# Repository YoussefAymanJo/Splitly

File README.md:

## Splitly

## Description

corne  hybrid wireless keyboard based .As it consists of a left part keyboard  connected to pc wired ,and right part keyboard powered by a rechargeable Battery which can operate up to week and connected to left part via bluetooth.And operated by nice Nano and CAT display. And a  numpad with RGB colours, connected wired to pc and powered by pico rp2040 .
## Why it was built
I built this,beacause i always need full split mechanical keyboard,but i need to customize it features by myself.So this keyboard it custosmized to my needings.Also,it has customized features based on usage.Splitly is not just regular keybaord but,desgined to be my companion.
## How to use it / Build it
Firsly,printing all 3d models after that fabricate PCB.After that assemble mx switches,MCU and battery management of pcb.then assemble all this parts together.finally,upload firmware on nice nano and pico,the test all 
## Schematic
I made the schematic and keyboard matrix for the corne keyboard, then the  numpad  .

### Left Part

### Right Part

### Numpad

## PCB
I routed the pcb ,then i outlined the shape of 2 keboard parts and numpad .

### Left Part

### Right Part

### Numpad

## CAD
I started   sketching the plate for left & right part keyboard,the i the Enclosure , then the top cover.After that i worked on numpad  plate, then enclosure and top cover,finally i redered them all.

### Left Part

### Right Part

### Numpad

## Firmware
I used kmk with CircuitPython as firmware,and made code for the left  & right part which is keyboard and the numpad

### Left Part

### Right Part

### Numpad

## BOM 
I made the BOM  and needed materials ,in egypt then convert its price to USD dollar.

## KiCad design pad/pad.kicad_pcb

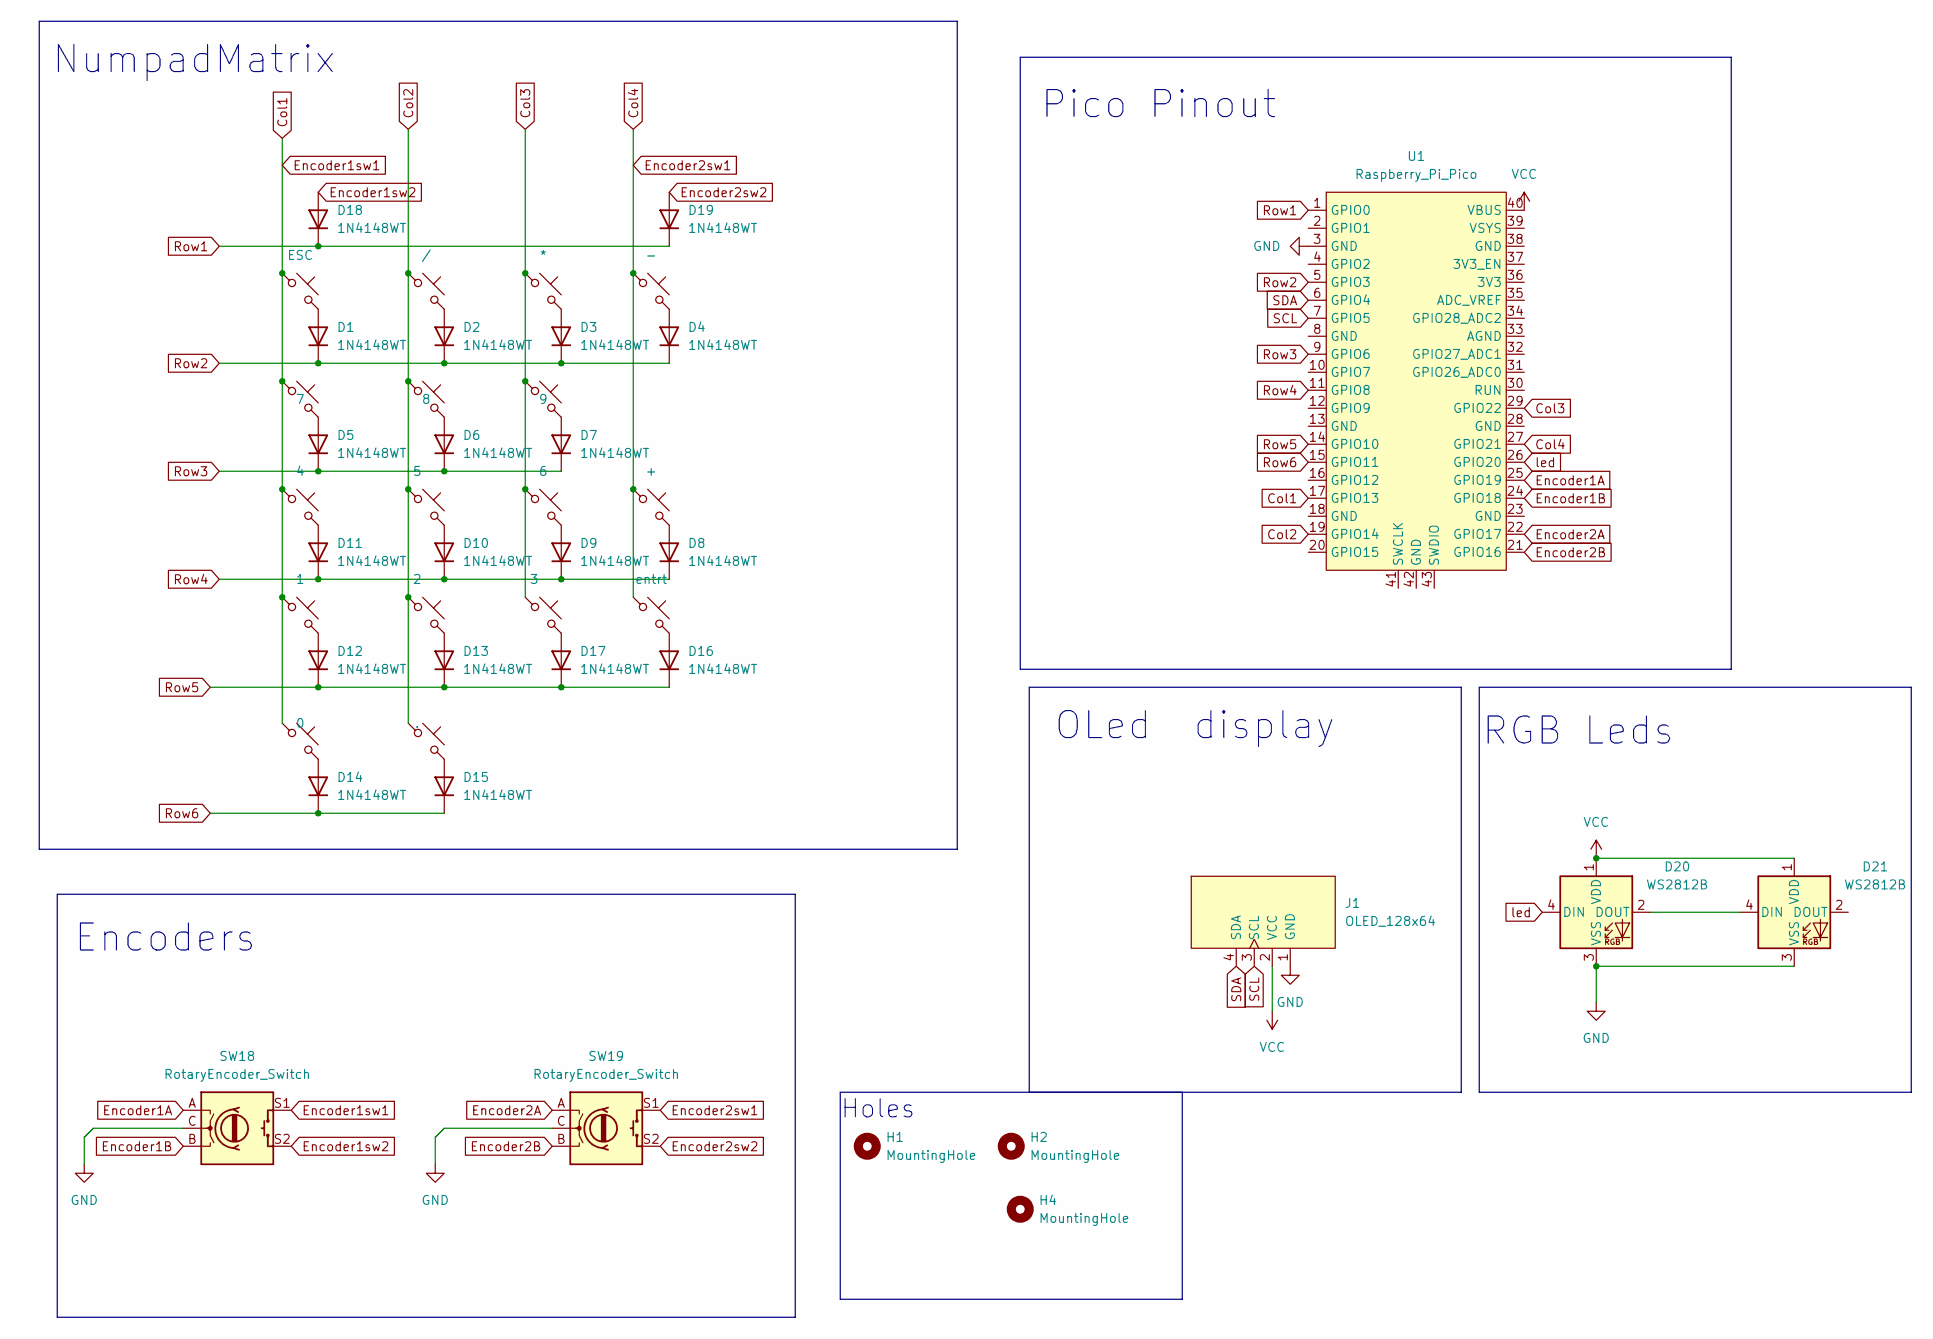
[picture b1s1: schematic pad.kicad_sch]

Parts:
D1, D2, D3, D4, D5, D6, D7, D8, D9, D10, D11, D12, D13, D14, D15, D16, D17, D18, D19: 1N4148WT; Diode_DO-35
D20, D21: WS2812B; LED_WS2812B_PLCC4_5.0x5.0mm_P3.2mm
H1, H2, H4: MountingHole; MountingHole_3.2mm_M3
J1: OLED_128x64
SW1: ESC; MX_PCB_1.00u
SW2: /; MX_PCB_1.00u
SW3: *; MX_PCB_1.00u
SW4: -; MX_PCB_1.00u
SW5: 7; MX_PCB_1.00u
SW6: 8; MX_PCB_1.00u
SW7: 9; MX_PCB_1.00u
SW8: +; MX_PCB_2.00u
SW9: 4; MX_PCB_1.00u
SW10: 5; MX_PCB_1.00u
SW11: 6; MX_PCB_1.00u
SW12: 1; MX_PCB_1.00u
SW13: 2; MX_PCB_1.00u
SW14: 3; MX_PCB_1.00u
SW15: entrt; MX_PCB_2.00u
SW16: 0; MX_PCB_2.00u
SW17: .; MX_PCB_1.00u
SW18, SW19: RotaryEncoder_Switch; RotaryEncoder_Alps_EC11E-Switch_Vertical_H20mm_MountingHoles
U1: Raspberry_Pi_Pico

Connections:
Col1: SW1.1, SW5.1, SW9.1, SW12.1, SW16.1, SW18.S1, U1.17 (GPIO13)
Col2: SW2.1, SW6.1, SW10.1, SW13.1, SW17.1, U1.19 (GPIO14)
Col3: SW3.1, SW7.1, SW11.1, SW14.1, U1.29 (GPIO22)
Col4: SW4.1, SW8.1, SW15.1, SW19.S1, U1.27 (GPIO21)
Encoder1A: SW18.A, U1.25 (GPIO19)
Encoder1B: SW18.B, U1.24 (GPIO18)
Encoder1sw2: D18.2 (A), SW18.S2
Encoder2A: SW19.A, U1.22 (GPIO17)
Encoder2B: SW19.B, U1.21 (GPIO16)
Encoder2sw2: D19.2 (A), SW19.S2
GND: D20.3 (VSS), D21.3 (VSS), J1.1 (GND), SW18.C, SW19.C, U1.3 (GND)
unnamed: D1.2 (A), SW1.2
unnamed: D2.2 (A), SW2.2
unnamed: D3.2 (A), SW3.2
unnamed: D4.2 (A), SW4.2
unnamed: D5.2 (A), SW5.2
unnamed: D6.2 (A), SW6.2
unnamed: D7.2 (A), SW7.2
unnamed: D8.2 (A), SW8.2
unnamed: D9.2 (A), SW11.2
unnamed: D10.2 (A), SW10.2
unnamed: D11.2 (A), SW9.2
unnamed: D12.2 (A), SW12.2
unnamed: D13.2 (A), SW13.2
unnamed: D14.2 (A), SW16.2
unnamed: D15.2 (A), SW17.2
unnamed: D16.2 (A), SW15.2
unnamed: D17.2 (A), SW14.2
unnamed: D20.2 (DOUT), D21.4 (DIN)
Row1: D18.1 (K), D19.1 (K), U1.1 (GPIO0)
Row2: D1.1 (K), D2.1 (K), D3.1 (K), D4.1 (K), U1.5 (GPIO3)
Row3: D5.1 (K), D6.1 (K), D7.1 (K), U1.9 (GPIO6)
Row4: D8.1 (K), D9.1 (K), D10.1 (K), D11.1 (K), U1.11 (GPIO8)
Row5: D12.1 (K), D13.1 (K), D16.1 (K), D17.1 (K), U1.14 (GPIO10)
Row6: D14.1 (K), D15.1 (K), U1.15 (GPIO11)
SCL: J1.3 (SCL), U1.7 (GPIO5)
SDA: J1.4 (SDA), U1.6 (GPIO4)
VCC: D20.1 (VDD), D21.1 (VDD), J1.2 (VCC), U1.40 (VBUS)
led: D20.4 (DIN), U1.26 (GPIO20)

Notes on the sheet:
Encoders
Pico Pinout
RGB Leds
Holes
OLed display
NumpadMatrix

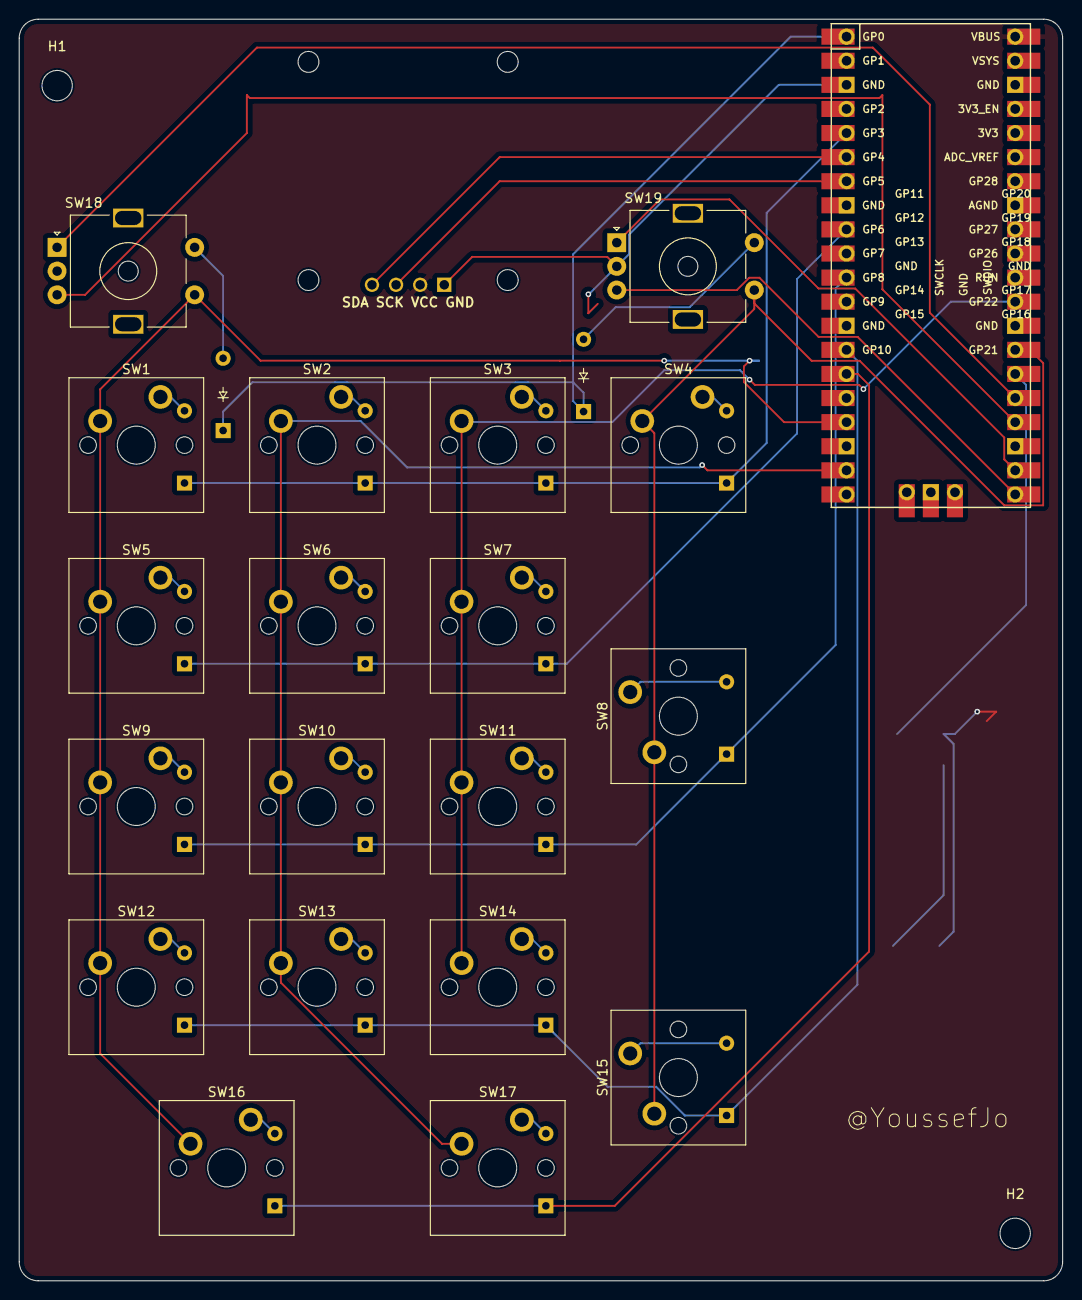
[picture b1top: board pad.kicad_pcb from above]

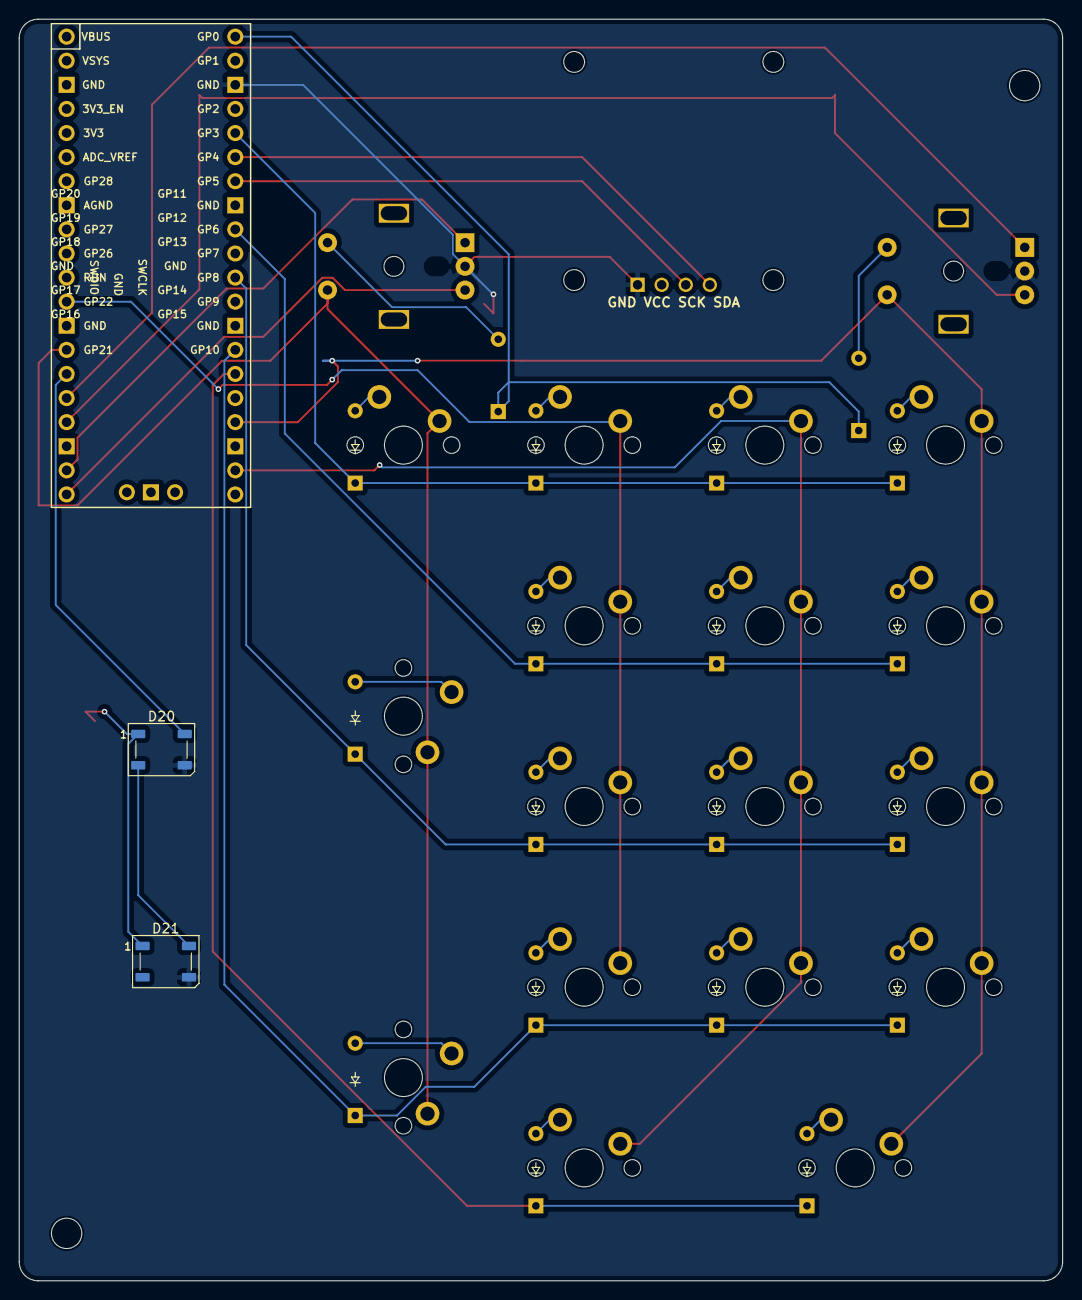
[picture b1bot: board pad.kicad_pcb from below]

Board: 2 copper layers, 110.0 x 133.0 mm, 45 parts (19 on the bottom side), 39 nets.

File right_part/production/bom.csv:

Designator,Footprint,Quantity,Value,LCSC Part #
"D1, D10, D11, D12, D13, D14, D15, D16, D17, D18, D19, D2, D20, D21, D3, D4, D5, D6, D7, D8, D9",Diode_DO-35,21,~,
J1,JST_PH_S2B-PH-K_1x02_P2.00mm_Horizontal,1,Conn_01x02_Pin,
SW1,MX_PCB_1.00u,1,I,
SW10,MX_PCB_1.00u,1,H,
SW11,MX_PCB_1.00u,1,;,
SW12,MX_PCB_1.00u,1,Alt,
SW13,MX_PCB_1.00u,1,",",
SW14,MX_PCB_1.00u,1,M,
SW15,MX_PCB_1.00u,1,.,
SW16,MX_PCB_1.00u,1,N,
SW17,MX_PCB_1.00u,1,/,
SW18,MX_PCB_1.00u,1,Func,
SW19,MX_PCB_1.00u,1,shift,
SW2,MX_PCB_1.00u,1,U,
SW20,MX_PCB_1.50u,1,bksp,
SW21,MX_PCB_1.00u,1,Space,
SW22,SW_Slide_SPDT_Angled_CK_OS102011MA1Q,1,SW_SPDT,
SW3,MX_PCB_1.00u,1,O,
SW4,MX_PCB_1.00u,1,Y,
SW5,MX_PCB_1.00u,1,P,
SW6,MX_PCB_1.00u,1,Del,
SW7,MX_PCB_1.00u,1,K,
SW8,MX_PCB_1.00u,1,J,
SW9,MX_PCB_1.00u,1,L,
U1,Nice_Nano_V2,1,Nice_Nano_V2,

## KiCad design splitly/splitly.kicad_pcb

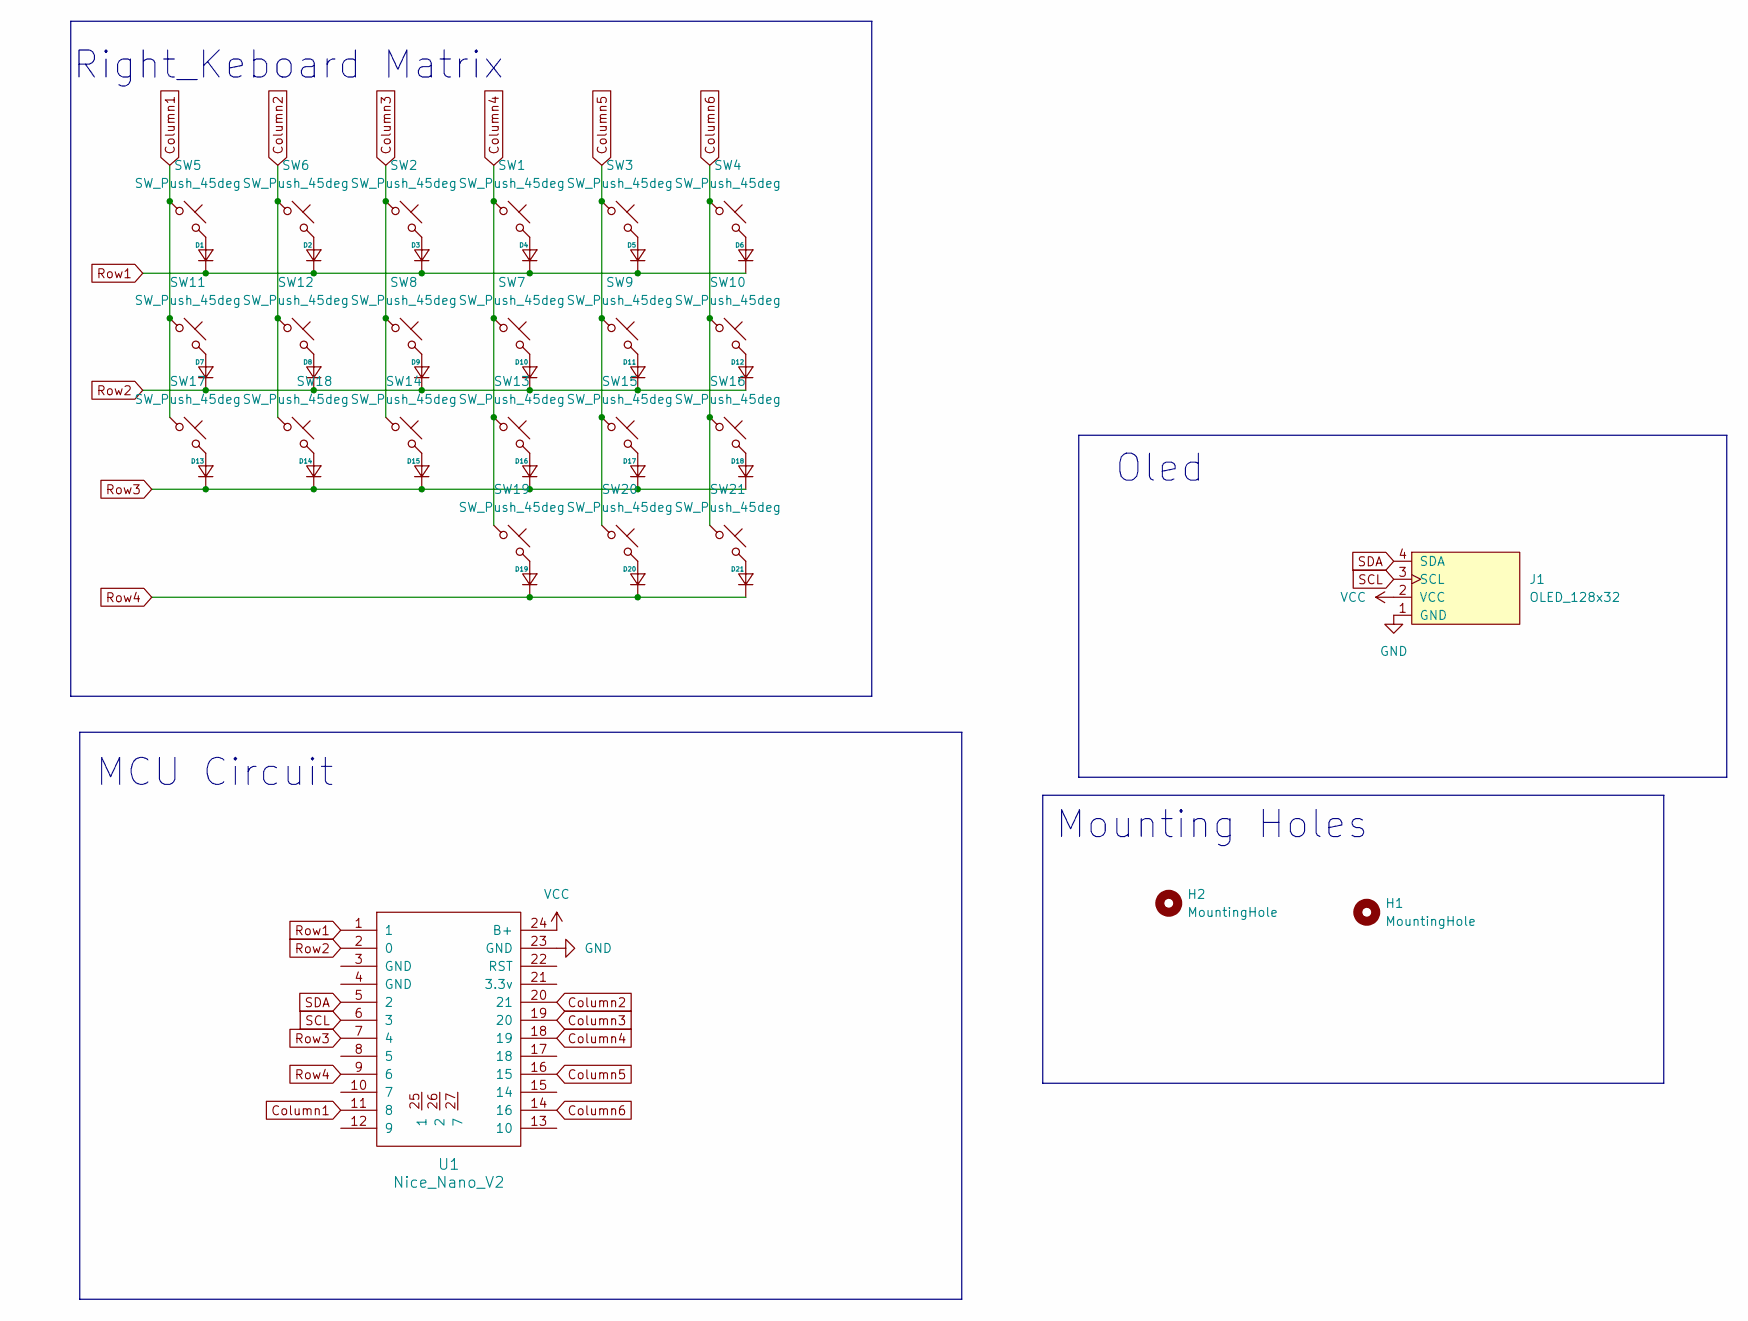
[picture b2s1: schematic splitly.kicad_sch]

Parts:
D1, D2, D3, D4, D5, D6, D7, D8, D9, D10, D11, D12, D13, D14, D15, D16, D17, D18, D19, D20, D21: Diode_DO-35
H1, H2: MountingHole; MountingHole_3.2mm_M3
J1: OLED_128x32
SW1, SW2, SW3, SW4, SW5, SW6, SW7, SW8, SW9, SW10, SW11, SW12, SW13, SW14, SW15, SW16, SW17, SW18, SW19, SW20: SW_Push_45deg; MX_PCB_1.00u
SW21: SW_Push_45deg; MX_PCB_1.50u
U1: Nice_Nano_V2

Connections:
Column1: SW5.1, SW11.1, SW17.1, U1.11 (8)
Column2: SW6.1, SW12.1, SW18.1, U1.20 (21)
Column3: SW2.1, SW8.1, SW14.1, U1.19 (20)
Column4: SW1.1, SW7.1, SW13.1, SW19.1, U1.18 (19)
Column5: SW3.1, SW9.1, SW15.1, SW20.1, U1.16 (15)
Column6: SW4.1, SW10.1, SW16.1, SW21.1, U1.14 (16)
GND: J1.1 (GND), U1.23 (GND)
unnamed: D1.2 (A), SW5.2
unnamed: D2.2 (A), SW6.2
unnamed: D3.2 (A), SW2.2
unnamed: D4.2 (A), SW1.2
unnamed: D5.2 (A), SW3.2
unnamed: D6.2 (A), SW4.2
unnamed: D7.2 (A), SW11.2
unnamed: D8.2 (A), SW12.2
unnamed: D9.2 (A), SW8.2
unnamed: D10.2 (A), SW7.2
unnamed: D11.2 (A), SW9.2
unnamed: D12.2 (A), SW10.2
unnamed: D13.2 (A), SW17.2
unnamed: D14.2 (A), SW18.2
unnamed: D15.2 (A), SW14.2
unnamed: D16.2 (A), SW13.2
unnamed: D17.2 (A), SW15.2
unnamed: D18.2 (A), SW16.2
unnamed: D19.2 (A), SW19.2
unnamed: D20.2 (A), SW20.2
unnamed: D21.2 (A), SW21.2
Row1: D1.1 (K), D2.1 (K), D3.1 (K), D4.1 (K), D5.1 (K), D6.1 (K), U1.1
Row2: D7.1 (K), D8.1 (K), D9.1 (K), D10.1 (K), D11.1 (K), D12.1 (K), U1.2 (0)
Row3: D13.1 (K), D14.1 (K), D15.1 (K), D16.1 (K), D17.1 (K), D18.1 (K), U1.7 (4)
Row4: D19.1 (K), D20.1 (K), D21.1 (K), U1.9 (6)
SCL: J1.3 (SCL), U1.6 (3)
SDA: J1.4 (SDA), U1.5 (2)
VCC: J1.2 (VCC), U1.24 (B+)

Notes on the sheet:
Right_Keboard Matrix
MCU Circuit
Mounting Holes
Oled

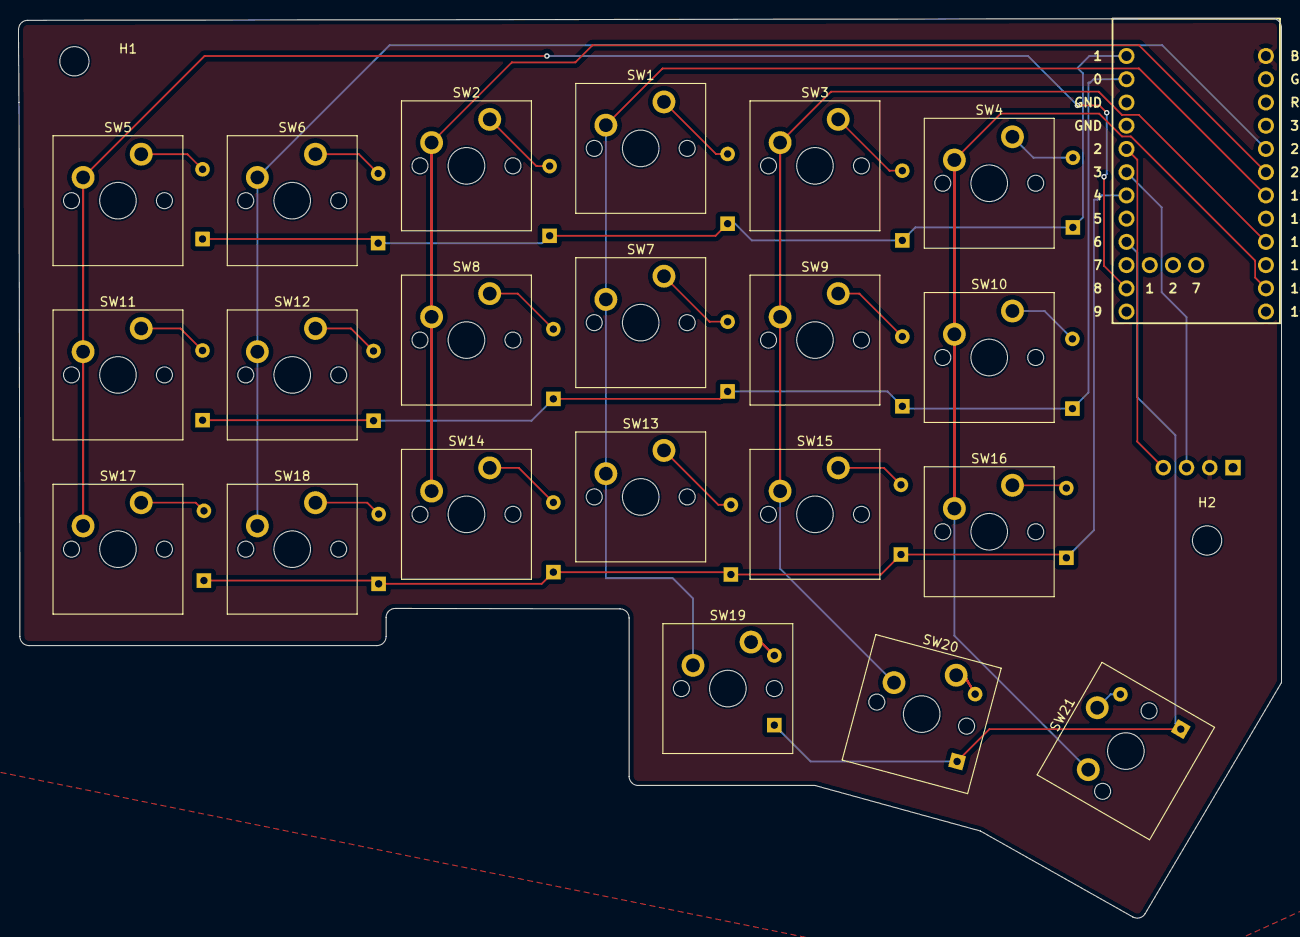
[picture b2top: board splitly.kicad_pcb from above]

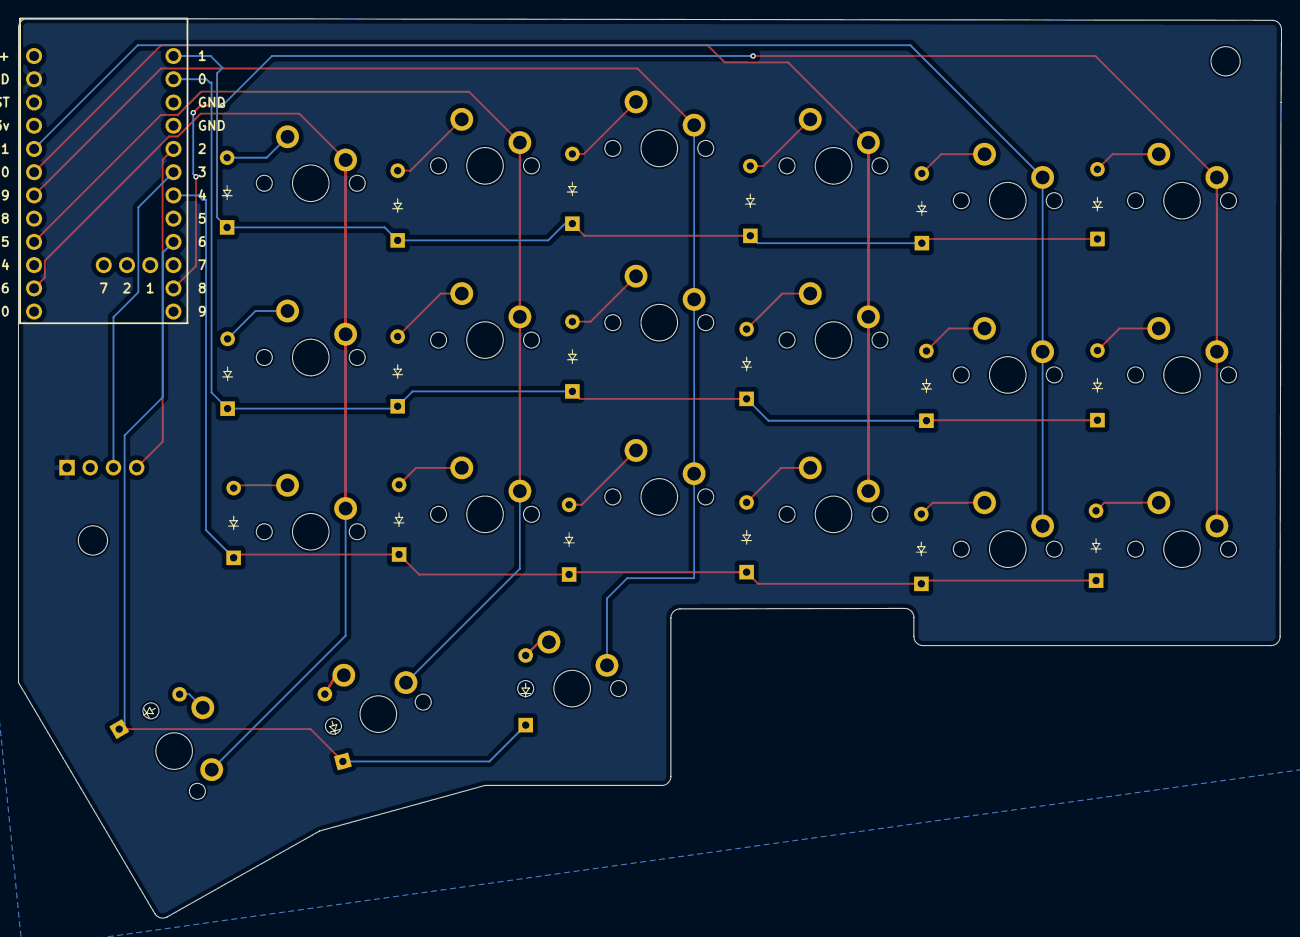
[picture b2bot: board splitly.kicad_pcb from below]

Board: 2 copper layers, 138.1 x 98.3 mm, 46 parts (21 on the bottom side), 35 nets.

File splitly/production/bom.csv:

Designator,Footprint,Quantity,Value,LCSC Part #
"D1, D10, D11, D12, D13, D14, D15, D16, D17, D18, D19, D2, D20, D21, D3, D4, D5, D6, D7, D8, D9",Diode_DO-35,21,~,
J1,OLED_128x32,1,OLED_128x32,
"SW1, SW10, SW11, SW12, SW13, SW14, SW15, SW16, SW17, SW18, SW19, SW2, SW20, SW3, SW4, SW5, SW6, SW7, SW8, SW9",MX_PCB_1.00u,20,SW_Push_45deg,
SW21,MX_PCB_1.50u,1,SW_Push_45deg,
U1,Nice_Nano_V2,1,Nice_Nano_V2,
